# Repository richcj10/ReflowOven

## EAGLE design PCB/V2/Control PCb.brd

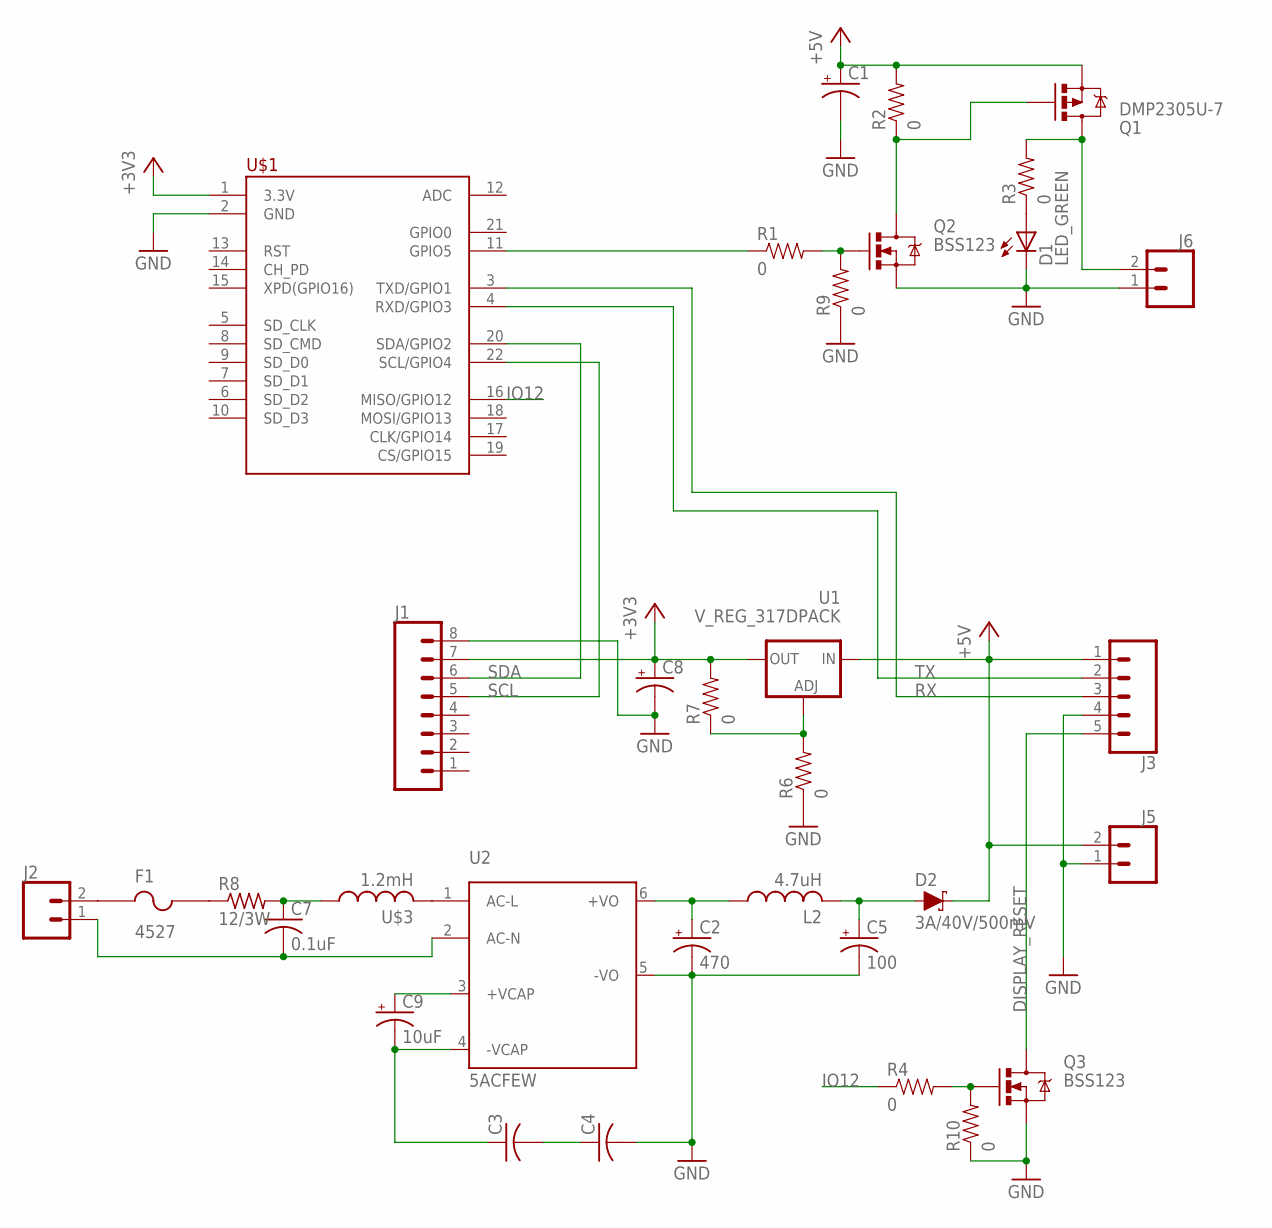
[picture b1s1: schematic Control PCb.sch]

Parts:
C1, C8: CPOL-USE2,5-6E; E2,5-6E
C2: 470; CPOL-RADIAL-5MM-10MM-KIT
C3, C4: C-USC1210; C1210
C5: 100; CPOL-RADIAL-5MM-10MM-KIT
C7: 0.1uF; C102-064X133
C9: 10uF; CPOL-RADIAL-5MM-10MM-KIT
D1: LED_GREEN; CHIP_LED0805
D2: 3A/40V/500mV; SMA-DIODE
F1: 4527
J1: CONN_08LOCK_LONGPADS; 1X08_LOCK_LONGPADS
J2, J5, J6: CONN_025MM; SCREWTERMINAL-5MM-2
J3: CONN_05LOCK_LONGPADS; 1X05_LOCK_LONGPADS
L2: 4.7uH; 6000
Q1: DMP2305U-7; SOT23
Q2, Q3: BSS123; SOT23
R1, R2, R3, R4, R6, R7, R9, R10: 0; 0805
R8: 12/3W; P0817V
U1: V_REG_317DPACK; V-REG_DPACK
U2: 5ACFEW
U$1: OLIMEX_MOD-WIFI-ESP8266-DEV>PINS-INSIDE; OLIMEX_MOD-WIFI-ESP8266-DEV-PINS-INSIDE
U$3: 1.2mH; 1800R

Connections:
+3V3: C8.+, J1.7, R7.2, U1.4 (OUT), U$1.1 (3.3V)
+5V: C1.+, D2.C, J3.1, J5.2, Q1.3 (S), R2.2, U1.3 (IN)
DISPLAY_RESET: J3.5, Q3.3 (D)
GND: C1.-, C2.-, C4.2, C5.-, C8.-, D1.C, J1.8, J3.4, J5.1, J6.1, Q2.2 (S), Q3.2 (S), R6.1, R9.1, R10.1, U2.5 (-VO), U$1.2 (GND)
IO12: R4.1, U$1.16 (MISO/GPIO12)
unnamed: D1.A, R3.1
unnamed: Q2.1 (G), R1.2, R9.2
unnamed: F1.1, J2.2
unnamed: C7.2, J2.1, U2.2 (AC-N)
unnamed: Q1.1 (G), Q2.3 (D), R2.1
unnamed: J6.2, Q1.2 (D), R3.2
unnamed: R1.1, U$1.11 (GPIO5)
unnamed: Q3.1 (G), R4.2, R10.2
unnamed: R6.2, R7.1, U1.1 (ADJ)
unnamed: F1.2, R8.1
unnamed: C7.1, R8.2, U$3.1
unnamed: U2.1 (AC-L), U$3.2
unnamed: C9.+, U2.3 (+VCAP)
unnamed: C3.1, C9.-, U2.4 (-VCAP)
unnamed: C3.2, C4.1
unnamed: C2.+, L2.1, U2.6 (+VO)
unnamed: C5.+, D2.A, L2.2
RX: J3.3, U$1.3 (TXD/GPIO1)
SCL: J1.5, U$1.22 (SCL/GPIO4)
SDA: J1.6, U$1.20 (SDA/GPIO2)
TX: J3.2, U$1.4 (RXD/GPIO3)

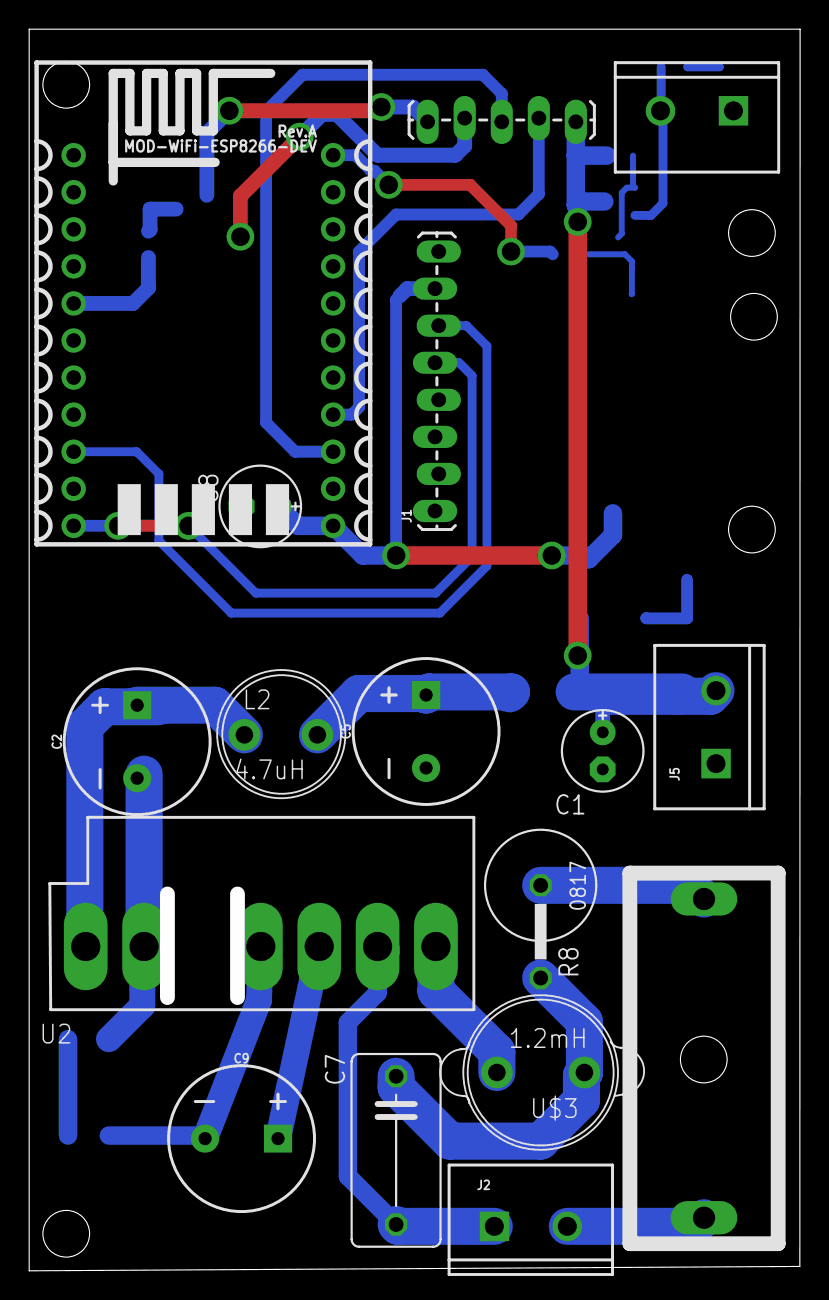
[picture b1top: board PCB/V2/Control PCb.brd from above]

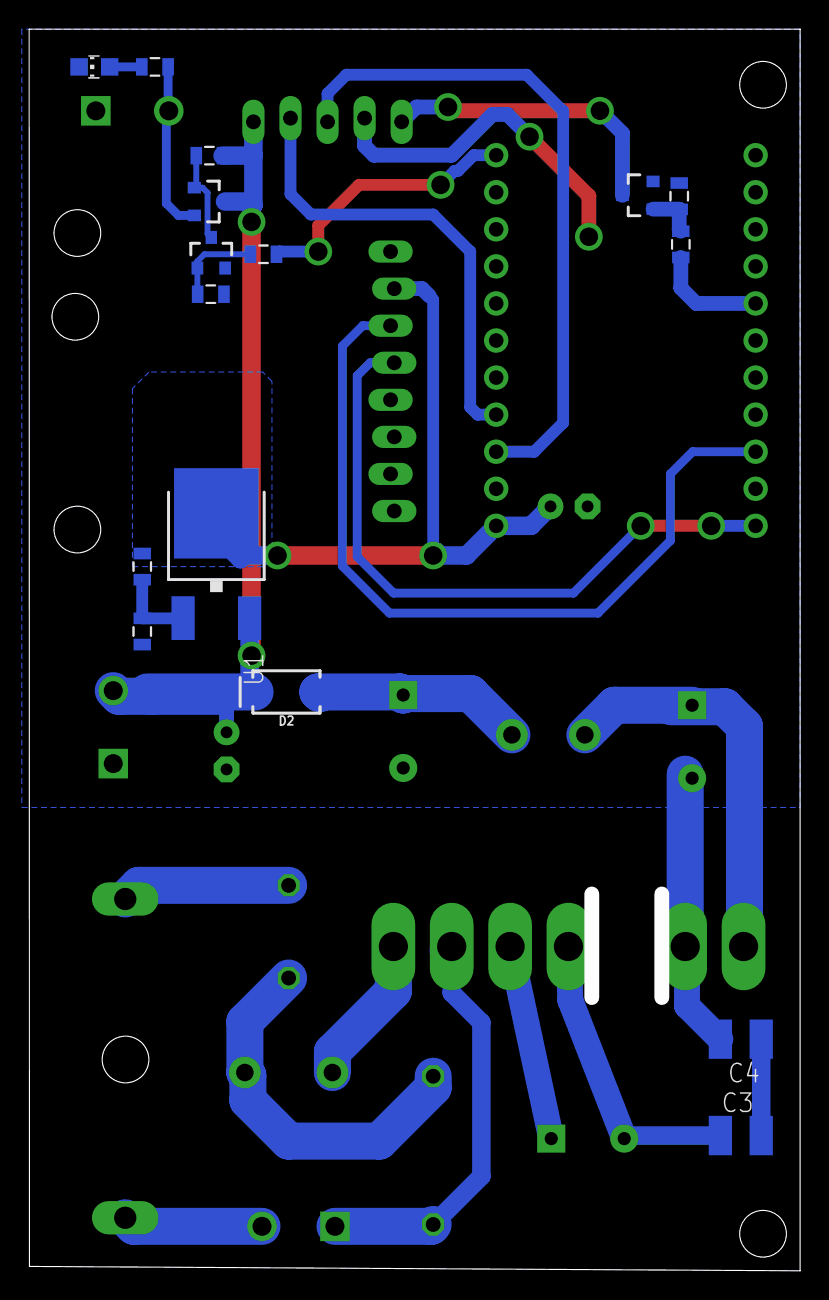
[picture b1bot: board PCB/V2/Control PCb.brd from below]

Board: 2 copper layers, 51.8 x 84.1 mm, 33 parts (16 on the bottom side), 26 nets.

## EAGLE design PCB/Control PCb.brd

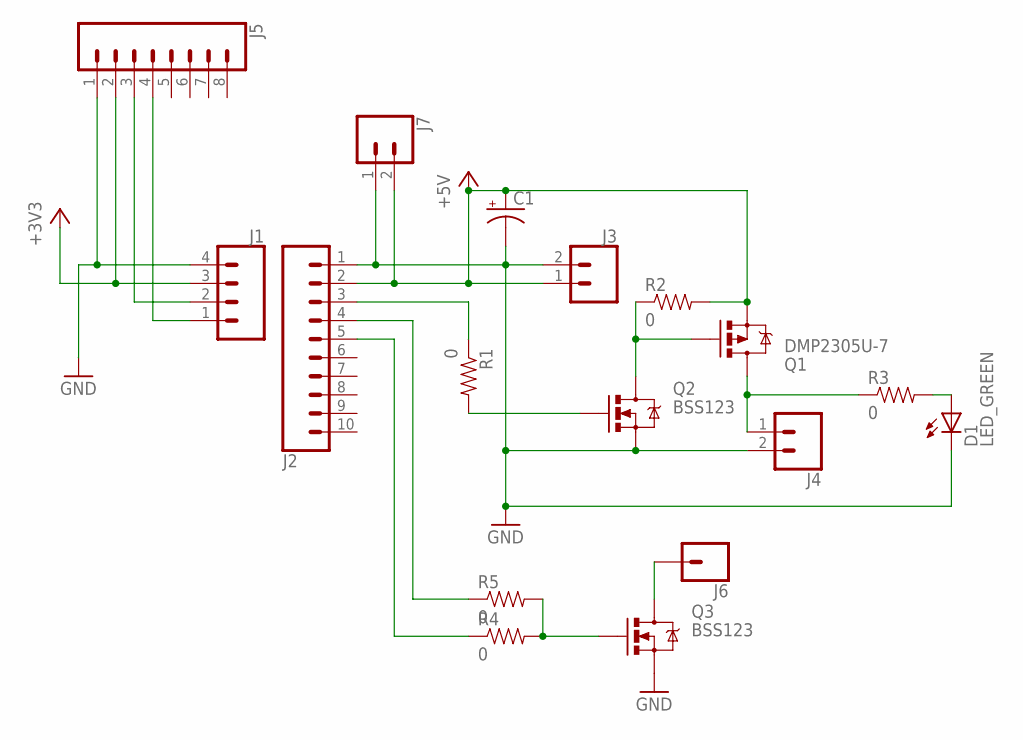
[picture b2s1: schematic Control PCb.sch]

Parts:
C1: CPOL-USE2,5-6E; E2,5-6E
D1: LED_GREEN; CHIP_LED0805
J1: CONN_04LOCK_LONGPADS; 1X04_LOCK_LONGPADS
J2: CONN_10LOCK_LONGPADS; 1X10_LOCK_LONGPADS
J3, J4: CONN_023.5MM; SCREWTERMINAL-3.5MM-2
J5: CONN_08LOCK_LONGPADS; 1X08_LOCK_LONGPADS
J6: CONN_01OFFSET; 1X01_OFFSET
J7: CONN_02LOCK_LONGPADS; 1X02_LOCK_LONGPADS
Q1: DMP2305U-7; SOT23
Q2, Q3: BSS123; SOT23
R1, R2, R3, R4, R5: 0; 0805

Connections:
+3V3: J1.3, J5.2
+5V: C1.+, J2.2, J3.1, J7.2, Q1.3 (S), R2.2
GND: C1.-, D1.C, J1.4, J2.1, J3.2, J4.2, J5.1, J7.1, Q2.2 (S), Q3.2 (S)
unnamed: J2.3, R1.1
unnamed: Q2.1 (G), R1.2
unnamed: J1.2, J5.3
unnamed: J1.1, J5.4
unnamed: Q1.1 (G), Q2.3 (D), R2.1
unnamed: J4.1, Q1.2 (D), R3.1
unnamed: D1.A, R3.2
unnamed: Q3.1 (G), R4.2, R5.2
unnamed: J2.5, R4.1
unnamed: J2.4, R5.1
unnamed: J6.1, Q3.3 (D)

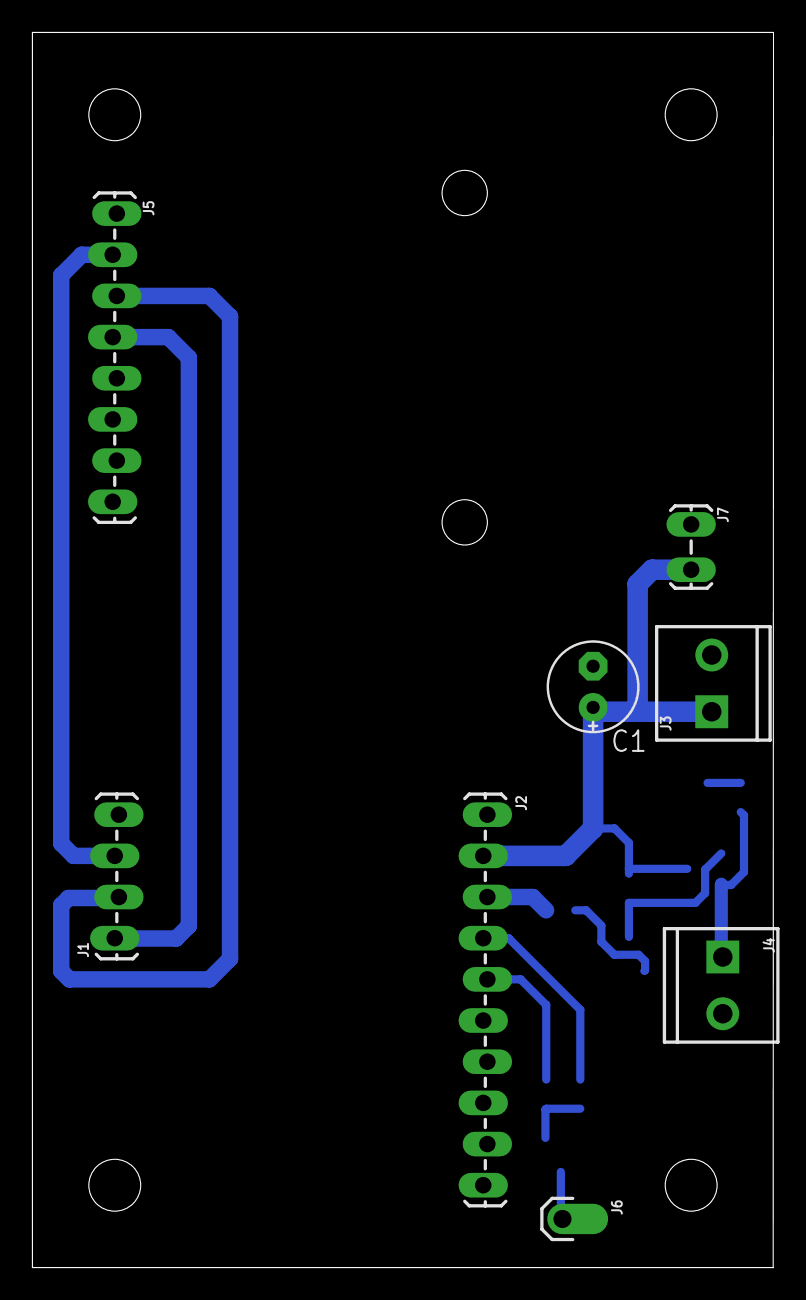
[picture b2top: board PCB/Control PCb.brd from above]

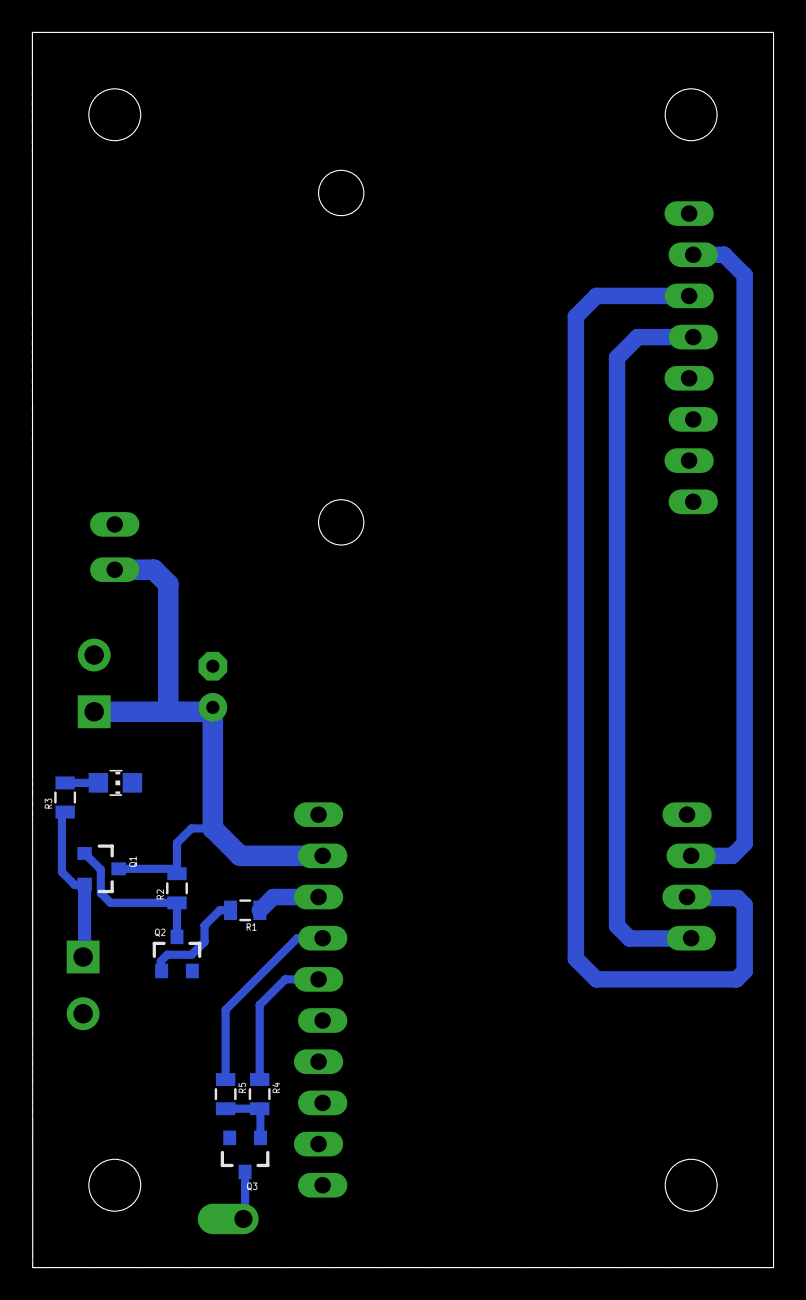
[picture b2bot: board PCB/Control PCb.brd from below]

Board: 2 copper layers, 45.7 x 76.2 mm, 17 parts (9 on the bottom side), 14 nets.

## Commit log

2022-01-05 Adding code for the PID controller and GUI
2022-01-05 Added code
2022-01-09 got data coming from wepage
2022-01-10 Wifi Config Works - added 4MB flash modifier and Power Control Drive
2022-01-17 PCB files etc
2022-01-20 PCB Work
2022-01-24 PCB + ArduinoOTA working
2022-01-26 Webpage work
2022-01-26 Web page work
2022-01-27 More Webpage work
2022-02-07 Code + PCB stuff
2022-02-07 Screen Code
2022-02-08 Added code for display
2022-02-17 Reflow oven working!
2022-02-23 Added GUI debug
2023-02-19 Some Screen Work
2023-09-05 Worked on PID tune, set up to autorun clay
2023-09-17 Got baking done, PID is more tuned, kinda fixed offset, need to investigate that

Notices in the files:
parts and their libraries:
SparkFun-Connectors: Licensing: Creative Commons ShareAlike 4.0 International - https://creativecommons.org/licenses/by-sa/4.0
